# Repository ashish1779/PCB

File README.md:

# PCB
PCB Designed in Eagle software

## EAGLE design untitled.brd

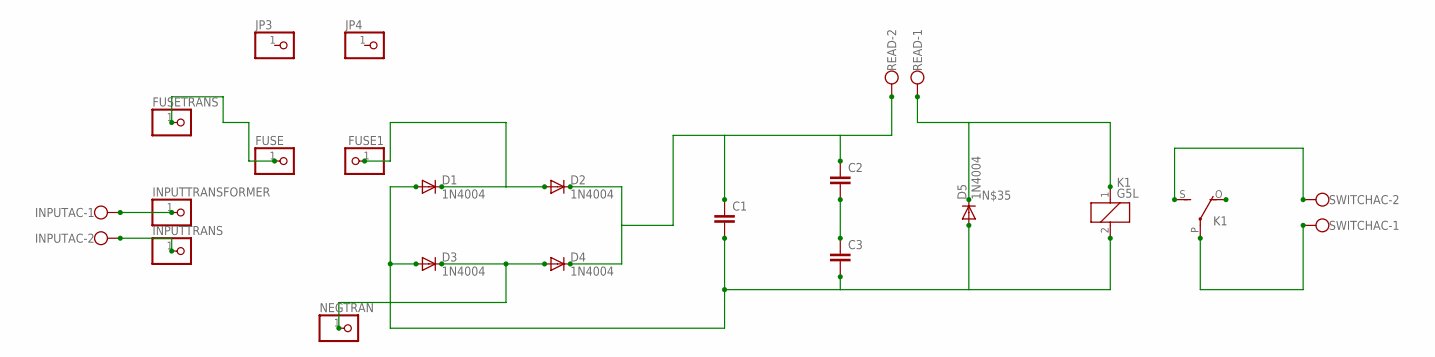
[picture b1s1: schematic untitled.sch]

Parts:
C1, C2, C3: CAPACITOR050-075X075; C050-075X075
D1, D2, D3, D4, D5: 1N4004; DO41-10
FUSE, FUSE1: PINHD-1X1; 1X01
FUSETRANS: PINHD-1X1; 1X01
INPUTAC: SCREW_TERMINAL_POWER; POWER_CONNECTOR
INPUTTRANS: PINHD-1X1; 1X01
INPUTTRANSFORMER: PINHD-1X1; 1X01
JP3, JP4: PINHD-1X1; 1X01
K1: G5L; G5LE
NEGTRAN: PINHD-1X1; 1X01
READ: SCREW_TERMINAL_POWER; POWER_CONNECTOR
SWITCHAC: SCREW_TERMINAL_POWER; POWER_CONNECTOR

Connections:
unnamed: D3.C, D4.A, NEGTRAN.1
unnamed: FUSE.1, FUSETRANS.1
unnamed: C1.2, C3.2, D1.A, D3.A, D5.A, K1.2
unnamed: D1.C, D2.A, FUSE1.1
unnamed: INPUTAC.1, INPUTTRANSFORMER.1
unnamed: INPUTAC.2, INPUTTRANS.1
unnamed: C1.1, C2.1, D2.C, D4.C, READ.2
unnamed: K1.P, SWITCHAC.1
unnamed: K1.S, SWITCHAC.2
unnamed: C2.2, C3.1
unnamed: D5.C, K1.1, READ.1

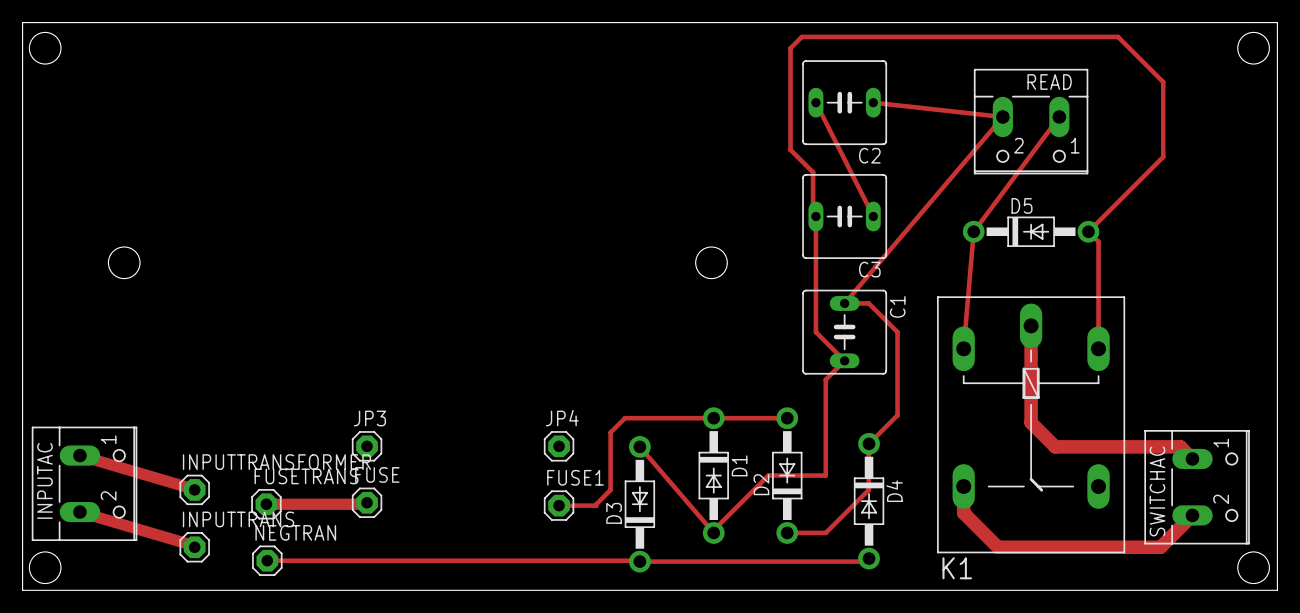
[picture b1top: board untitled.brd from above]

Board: 2 copper layers, 111.1 x 50.3 mm, 20 parts (0 on the bottom side), 11 nets.
